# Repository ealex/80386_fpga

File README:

This project is inspired by [Pierre Surply's article](https://blog.lse.epita.fr/articles/77-lsepc-intro.html) in LSE Blog

The board is based on:
- a 80386SX-16 CPU
- a CycloneII / IV EPxCy 
- XXX SDRAM

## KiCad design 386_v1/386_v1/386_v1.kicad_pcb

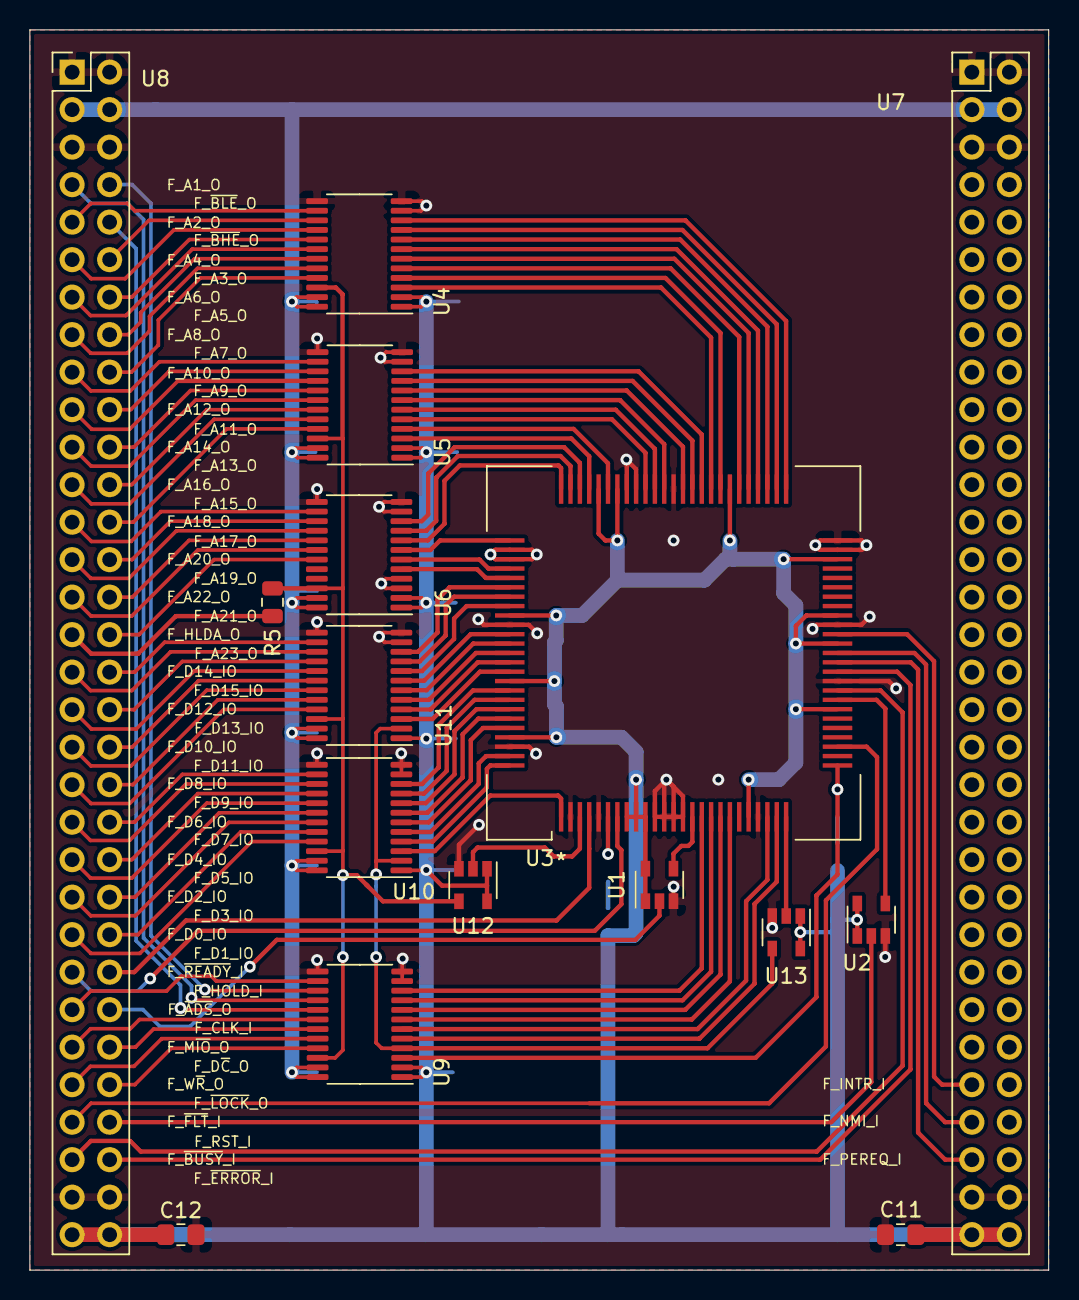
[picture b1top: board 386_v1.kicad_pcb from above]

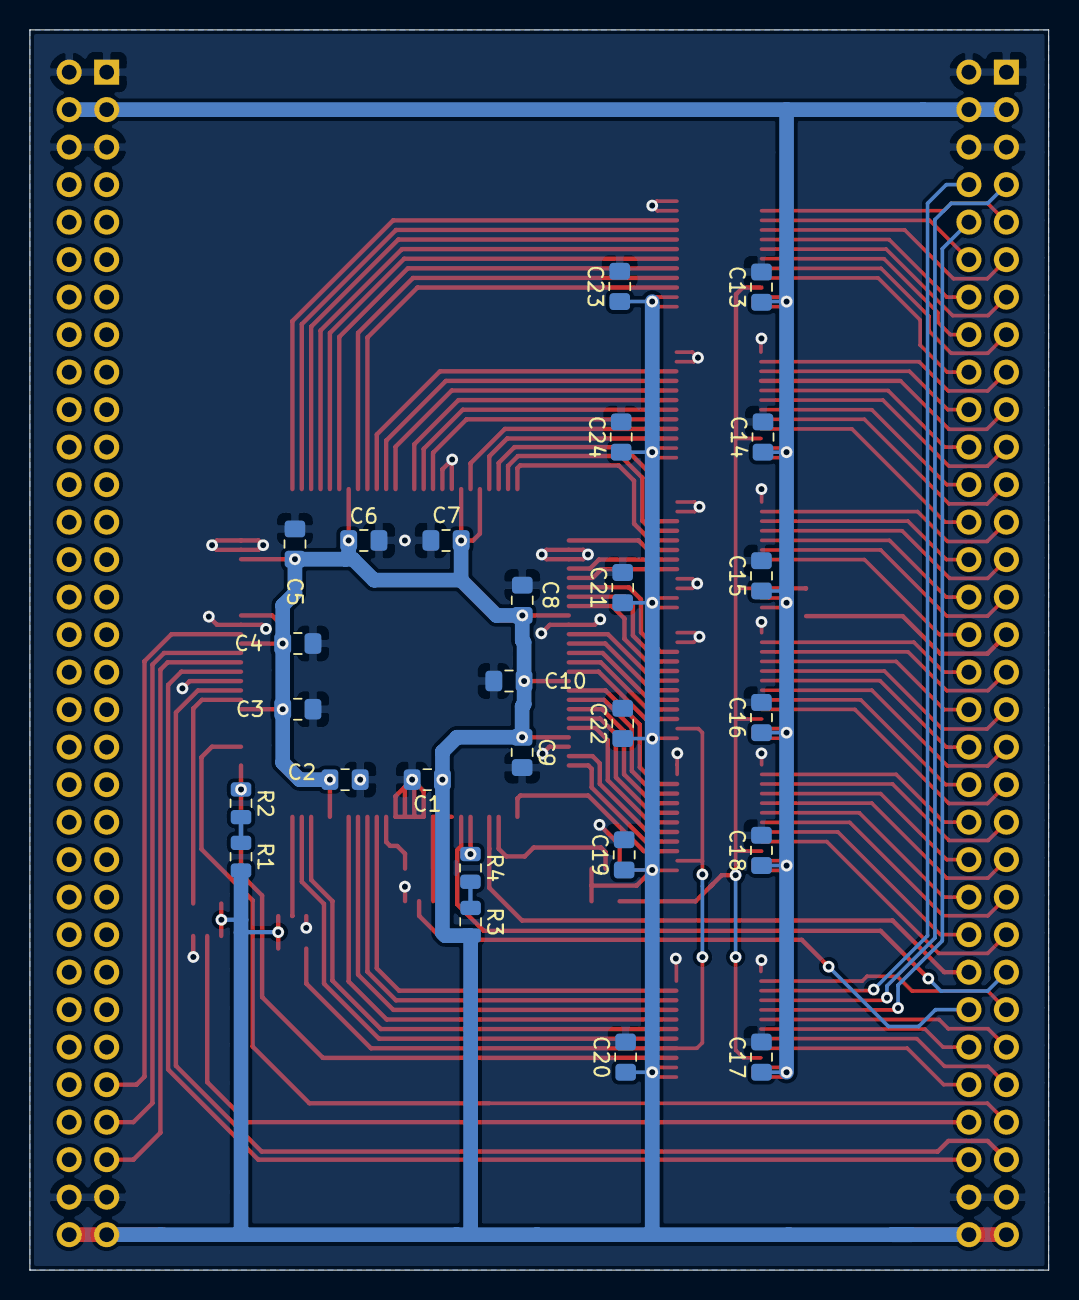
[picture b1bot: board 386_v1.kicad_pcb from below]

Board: 2 copper layers, 69.0 x 84.0 mm, 42 parts (26 on the bottom side), 114 nets.

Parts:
C1, C2, C3, C4, C5, C6, C7, C8, C9, C10, C11, C12, C13, C14, C15, C16, C17, C18, C19, C20, C21, C22, C23, C24: 100n; C_0805_2012Metric_Pad1.15x1.40mm_HandSolder
R1, R2, R3, R4, R5: 10k; R_0805_2012Metric
U1, U2, U12, U13: 74AHCT1G126; SOT-23-5
U3: i386SX; QFP-100_25x25_Pitch0.635mm
U4, U5, U6, U9, U10, U11: SN74LVC4245A; TSSOP-24_4.4x7.8mm_P0.65mm
U7, U8: Conn_02x32_Odd_Even; PinHeader_2x32_P2.54mm_Vertical

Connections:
+3V3: C13.1, C14.1, C15.1, C16.1, C17.1, C18.1, U4.23, U4.24, U5.23, U5.24, U6.23, U6.24, U7.3, U7.4, U8.3, U8.4, U9.23, U9.24, U10.23, U10.24, U11.23, U11.24
+5V: C1.1, C2.1, C3.1, C4.1, C5.1, C6.1, C7.1, C8.1, C9.1, C10.1, C11.1, C12.1, C19.1, C20.1, C21.1, C22.1, C23.1, C24.1, R1.2, R3.2, U1.1, U1.5, U2.1, U2.5, U3.8, U3.9, U3.10, U3.21, U3.32, U3.39, U3.42, U3.48, U3.57, U3.69, U3.71, U3.84, U3.91, U3.97, U4.1, U4.2, U5.1, U5.2, U6.1, U6.2, U7.63, U7.64, U8.63, U8.64, U9.1, U9.2, U10.1, U11.1, U12.1, U12.5, U13.1, U13.5
/A1: U3.18, U9.8
/A2: U3.51, U4.10
/A3: U3.52, U4.9
/A4: U3.53, U4.8
/A5: U3.54, U4.7
/A6: U3.55, U4.6
/A7: U3.56, U4.5
/A8: U3.58, U4.4
/A9: U3.59, U4.3
/A10: U3.60, U5.10
/A11: U3.61, U5.9
/A12: U3.62, U5.8
/A13: U3.64, U5.7
/A14: U3.65, U5.6
/A15: U3.66, U5.5
/A16: U3.70, U5.4
/A17: U3.72, U5.3
/A18: U3.73, U6.10
/A19: U3.74, U6.9
/A20: U3.75, U6.8
/A21: U3.76, U6.7
/A22: U3.79, U6.6
/A23: U3.80, U6.5
/D0: U3.1, U10.3
/D1: U3.100, U10.4
/D2: U3.99, U10.5
/D3: U3.96, U10.6
/D4: U3.95, U10.7
/D5: U3.94, U10.8
/D6: U3.93, U10.9
/D7: U3.92, U10.10
/D8: U3.90, U11.3
/D9: U3.89, U11.4
/D10: U3.88, U11.5
/D11: U3.87, U11.6
/D12: U3.86, U11.7
/D13: U3.83, U11.8
/D14: U3.82, U11.9
/D15: U3.81, U11.10
/D~C~_O: U3.24, U9.5
/F_A1_O: U8.7, U9.16
/F_A2_O: U4.14, U8.9
/F_A3_O: U4.15, U8.12
/F_A4_O: U4.16, U8.11
/F_A5_O: U4.17, U8.14
/F_A6_O: U4.18, U8.13
/F_A7_O: U4.19, U8.16
/F_A8_O: U4.20, U8.15
/F_A9_O: U4.21, U8.18
/F_A10_O: U5.14, U8.17
/F_A11_O: U5.15, U8.20
/F_A12_O: U5.16, U8.19
/F_A13_O: U5.17, U8.22
/F_A14_O: U5.18, U8.21
/F_A15_O: U5.19, U8.24
/F_A16_O: U5.20, U8.23
/F_A17_O: U5.21, U8.26
/F_A18_O: U6.14, U8.25
/F_A19_O: U6.15, U8.28
/F_A20_O: U6.16, U8.27
/F_A21_O: U6.17, U8.30
/F_A22_O: U6.18, U8.29
/F_A23_O: U6.19, U8.32
/F_CLK_I: U1.2, U8.52
/F_D0_IO: U8.47, U10.21
/F_D1_IO: U8.48, U10.20
/F_D2_IO: U8.45, U10.19
/F_D3_IO: U8.46, U10.18
/F_D4_IO: U8.43, U10.17
/F_D5_IO: U8.44, U10.16
/F_D6_IO: U8.41, U10.15
/F_D7_IO: U8.42, U10.14
/F_D8_IO: U8.39, U11.21
/F_D9_IO: U8.40, U11.20
/F_D10_IO: U8.37, U11.19
/F_D11_IO: U8.38, U11.18
/F_D12_IO: U8.35, U11.17
/F_D13_IO: U8.36, U11.16
/F_D14_IO: U8.33, U11.15
/F_D15_IO: U8.34, U11.14
/F_D~C~_O: U8.54, U9.19
/F_HLDA_O: R5.1, U4.22, U5.22, U6.22, U9.22, U10.22, U11.22, U12.4
/F_HOLD_I: U3.4, U8.50
/F_INTR_I: U3.40, U7.55
/F_M~IO~_O: U8.53, U9.18
/F_NMI_I: U3.38, U7.57
/F_PEREQ_I: U3.37, U7.59
/F_RST_I: U2.2, U8.58
/F_W~R~_O: U8.55, U9.20
/F_~ADS~_O: U8.51, U9.14
/F_~BHE~_O: U8.10, U9.17
/F_~BLE~_O: U8.8, U9.15
/F_~BUSY~_I: U3.34, U8.59
/F_~ERROR~_I: U3.36, U8.60
/F_~FLT~_I: U3.28, U8.57
/F_~LOCK~_O: U8.56, U9.21
/F_~READY~_I: U3.7, U8.49
/HLDA_RAW: U3.3, U12.2
/M~IO~_O: U3.23, U9.6
/W~R~_O: U9.4, U10.2, U11.2, U13.4
/W~R~_O_RAW: U3.25, U13.2
/~ADS~_O: U3.16, U9.10
/~BHE: U3.19, U9.7
/~BLE: U3.17, U9.9
/~LOCK~_O: R2.1, U3.26, U9.3
GND: C1.2, C2.2, C3.2, C4.2, C5.2, C6.2, C7.2, C8.2, C9.2, C10.2, C11.2, C12.2, C13.2, C14.2, C15.2, C16.2, C17.2, C18.2, C19.2, C20.2, C21.2, C22.2, C23.2, C24.2, U1.3, U2.3, U3.2, U3.5, U3.11, U3.12, U3.13, U3.14, U3.22, U3.35, U3.41, U3.49, U3.50, U3.63, U3.67, U3.68, U3.77, U3.78, U3.85, U3.98, U4.11, U4.12, U4.13, U5.11, U5.12, U5.13, U6.3, U6.4, U6.11, U6.12, U6.13, U7.1, U7.2, U7.5, U7.6, U7.61, U7.62, U8.1, U8.2, U8.5, U8.6, U8.61, U8.62, U9.11, U9.12, U9.13, U10.11, U10.12, U10.13, U11.11, U11.12, U11.13, U12.3, U13.3
unnamed: R1.1, R2.2
unnamed: R3.1, R4.2
unnamed: R4.1, U3.6
unnamed: R5.2, U8.31
unnamed: U1.4, U3.15
unnamed: U2.4, U3.33

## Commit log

2020-01-23 create initial schematic and add datasheets
2020-01-28 add external documentation
2020-05-23 80386 schematic symbol
2020-05-23 update schematic
2020-06-02 prepare for pcb 1.0
2020-06-04 use stack-trough connector
2020-07-28 update schematic, use active level shifters
2020-07-28 schematic
2020-07-30 pcb with buffers
2020-09-24 production v2
